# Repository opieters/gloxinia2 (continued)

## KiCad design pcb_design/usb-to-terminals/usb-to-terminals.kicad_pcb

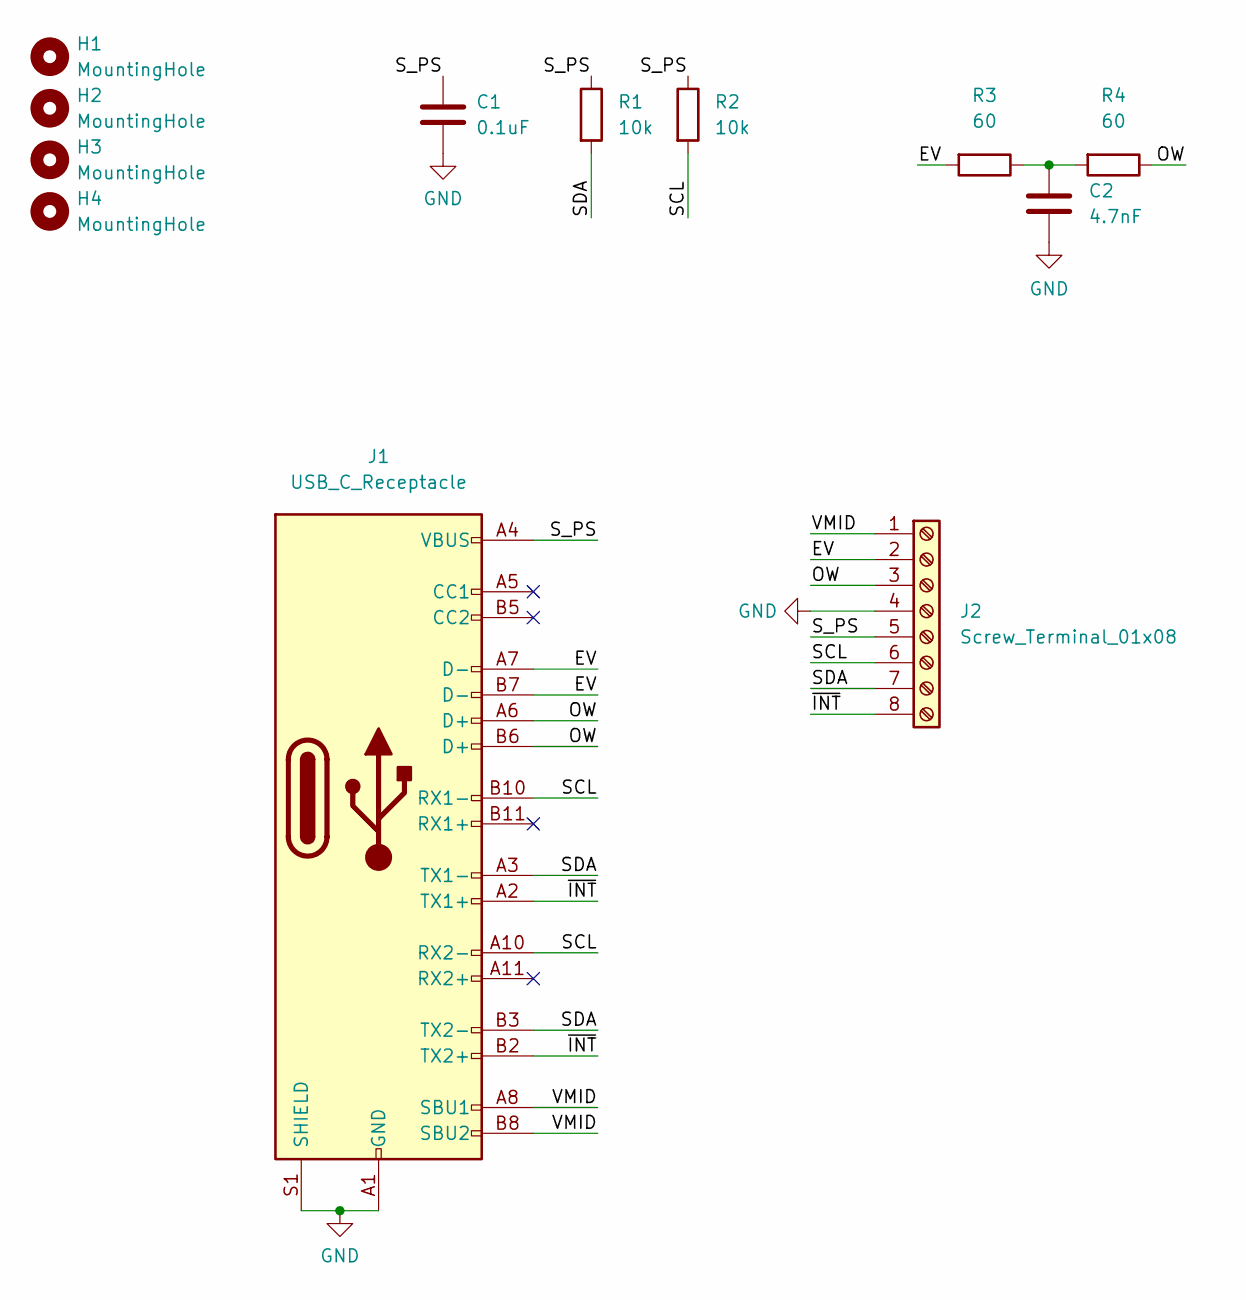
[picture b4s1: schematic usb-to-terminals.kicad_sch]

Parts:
C1: 0.1uF; C_0603_1608Metric; Voltage rating 16V; MPN C0603C104K4RAC7867
C2: 4.7nF; C_0603_1608Metric; Voltage rating 16V
H1, H2, H3, H4: MountingHole; MountingHole_3.2mm_M3
J1: USB_C_Receptacle; USB_C_Receptacle_Amphenol_12401861XX12A; MPN 124018612112A
J2: Screw_Terminal_01x08; TerminalBlock_Phoenix_PT-1,5-8-3.5-H_1x08_P3.50mm_Horizontal; MPN 1984646
R1, R2: 10k; R_0603_1608Metric
R3, R4: 60; R_0603_1608Metric

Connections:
/EV: J1.A7 (D-), J1.B7 (D-), J2.2, R3.2
/OW: J1.A6 (D+), J1.B6 (D+), J2.3, R4.1
/SCL: J1.A10 (RX2-), J1.B10 (RX1-), J2.6, R2.2
/SDA: J1.A3 (TX1-), J1.B3 (TX2-), J2.7, R1.2
/S_PS: C1.1, J1.A4 (VBUS), J1.A9 (VBUS), J1.B4 (VBUS), J1.B9 (VBUS), J2.5, R1.1, R2.1
/VMID: J1.A8 (SBU1), J1.B8 (SBU2), J2.1
/~INT: J1.A2 (TX1+), J1.B2 (TX2+), J2.8
GND: C1.2, C2.2, J1.A1 (GND), J1.A12 (GND), J1.B1 (GND), J1.B12 (GND), J1.S1 (SHIELD), J2.4
unnamed: C2.1, R3.1, R4.2

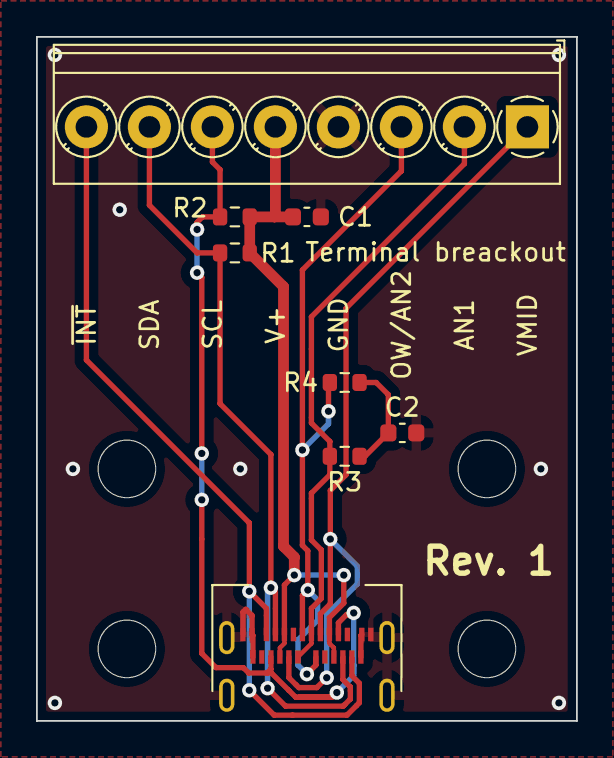
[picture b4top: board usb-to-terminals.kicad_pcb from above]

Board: 2 copper layers, 30.0 x 38.0 mm, 12 parts (0 on the bottom side), 9 nets.

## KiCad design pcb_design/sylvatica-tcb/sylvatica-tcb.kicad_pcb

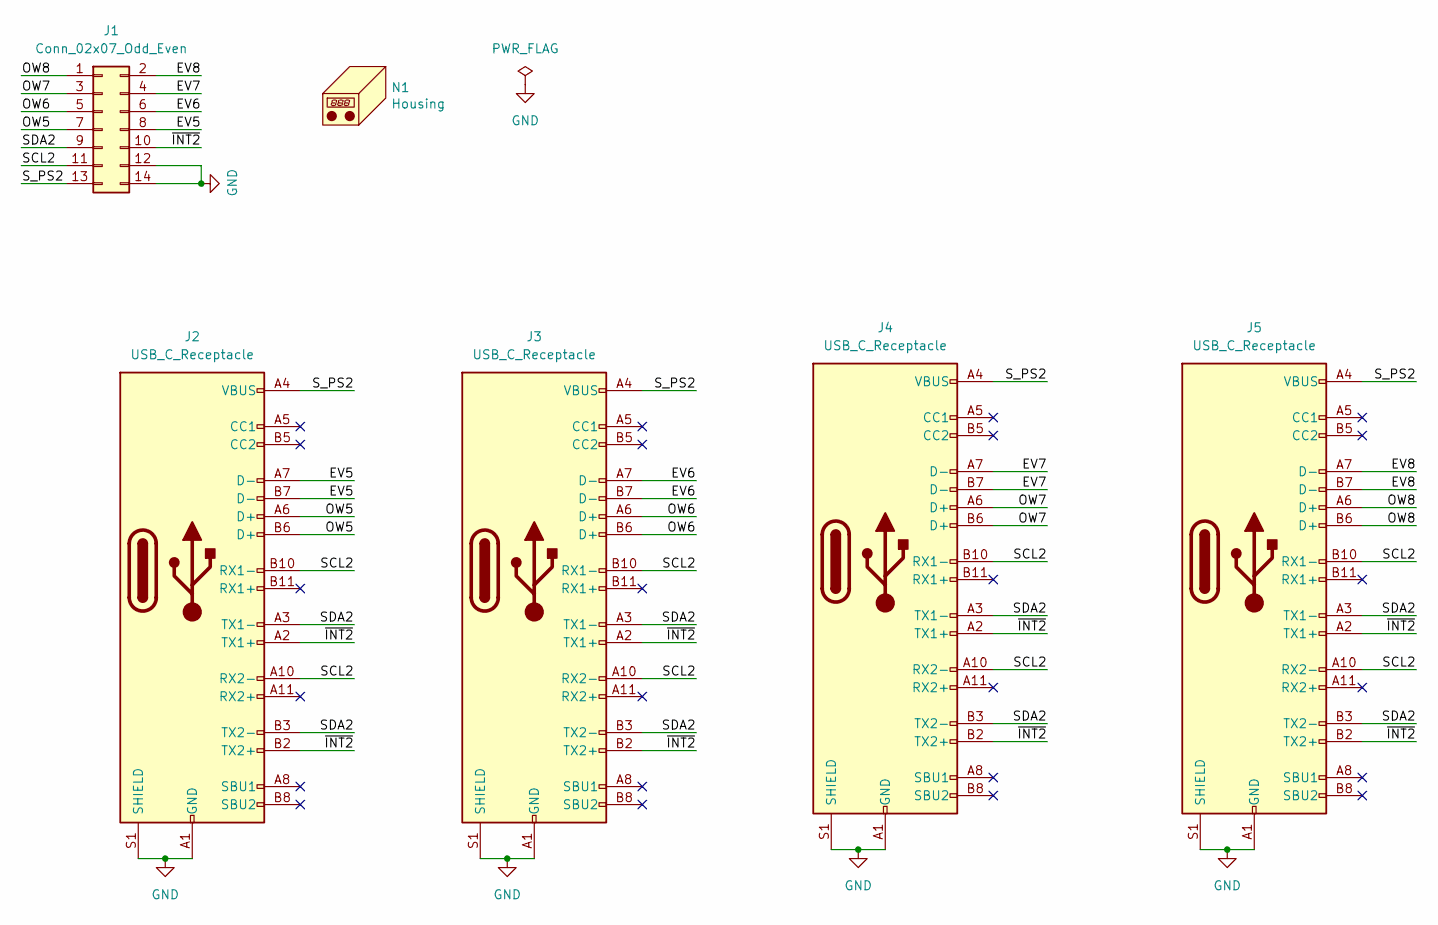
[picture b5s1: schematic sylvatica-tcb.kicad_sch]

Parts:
J1: Conn_02x07_Odd_Even; SAMTEC_TMMH-107-01-T-DV; MPN TMMH-107-01-T-DV
J2, J3, J4, J5: USB_C_Receptacle; USB_C_Receptacle_Amphenol_12401861XX12A; MPN 124018612112A
N1: Housing; Enclosure-Gloxinia4

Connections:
/EV5: J1.8, J2.A7 (D-), J2.B7 (D-)
/EV6: J1.6, J3.A7 (D-), J3.B7 (D-)
/EV7: J1.4, J4.A7 (D-), J4.B7 (D-)
/EV8: J1.2, J5.A7 (D-), J5.B7 (D-)
/OW5: J1.7, J2.A6 (D+), J2.B6 (D+)
/OW6: J1.5, J3.A6 (D+), J3.B6 (D+)
/OW7: J1.3, J4.A6 (D+), J4.B6 (D+)
/OW8: J1.1, J5.A6 (D+), J5.B6 (D+)
/SCL2: J1.11, J2.A10 (RX2-), J2.B10 (RX1-), J3.A10 (RX2-), J3.B10 (RX1-), J4.A10 (RX2-), J4.B10 (RX1-), J5.A10 (RX2-), J5.B10 (RX1-)
/SDA2: J1.9, J2.A3 (TX1-), J2.B3 (TX2-), J3.A3 (TX1-), J3.B3 (TX2-), J4.A3 (TX1-), J4.B3 (TX2-), J5.A3 (TX1-), J5.B3 (TX2-)
/S_PS2: J1.13, J2.A4 (VBUS), J2.A9 (VBUS), J2.B4 (VBUS), J2.B9 (VBUS), J3.A4 (VBUS), J3.A9 (VBUS), J3.B4 (VBUS), J3.B9 (VBUS), J4.A4 (VBUS), J4.A9 (VBUS), J4.B4 (VBUS), J4.B9 (VBUS), J5.A4 (VBUS), J5.A9 (VBUS), J5.B4 (VBUS), J5.B9 (VBUS)
/~INT2: J1.10, J2.A2 (TX1+), J2.B2 (TX2+), J3.A2 (TX1+), J3.B2 (TX2+), J4.A2 (TX1+), J4.B2 (TX2+), J5.A2 (TX1+), J5.B2 (TX2+)
GND: J1.12, J1.14, J2.A1 (GND), J2.A12 (GND), J2.B1 (GND), J2.B12 (GND), J2.S1 (SHIELD), J3.A1 (GND), J3.A12 (GND), J3.B1 (GND), J3.B12 (GND), J3.S1 (SHIELD), J4.A1 (GND), J4.A12 (GND), J4.B1 (GND), J4.B12 (GND), J4.S1 (SHIELD), J5.A1 (GND), J5.A12 (GND), J5.B1 (GND), J5.B12 (GND), J5.S1 (SHIELD)

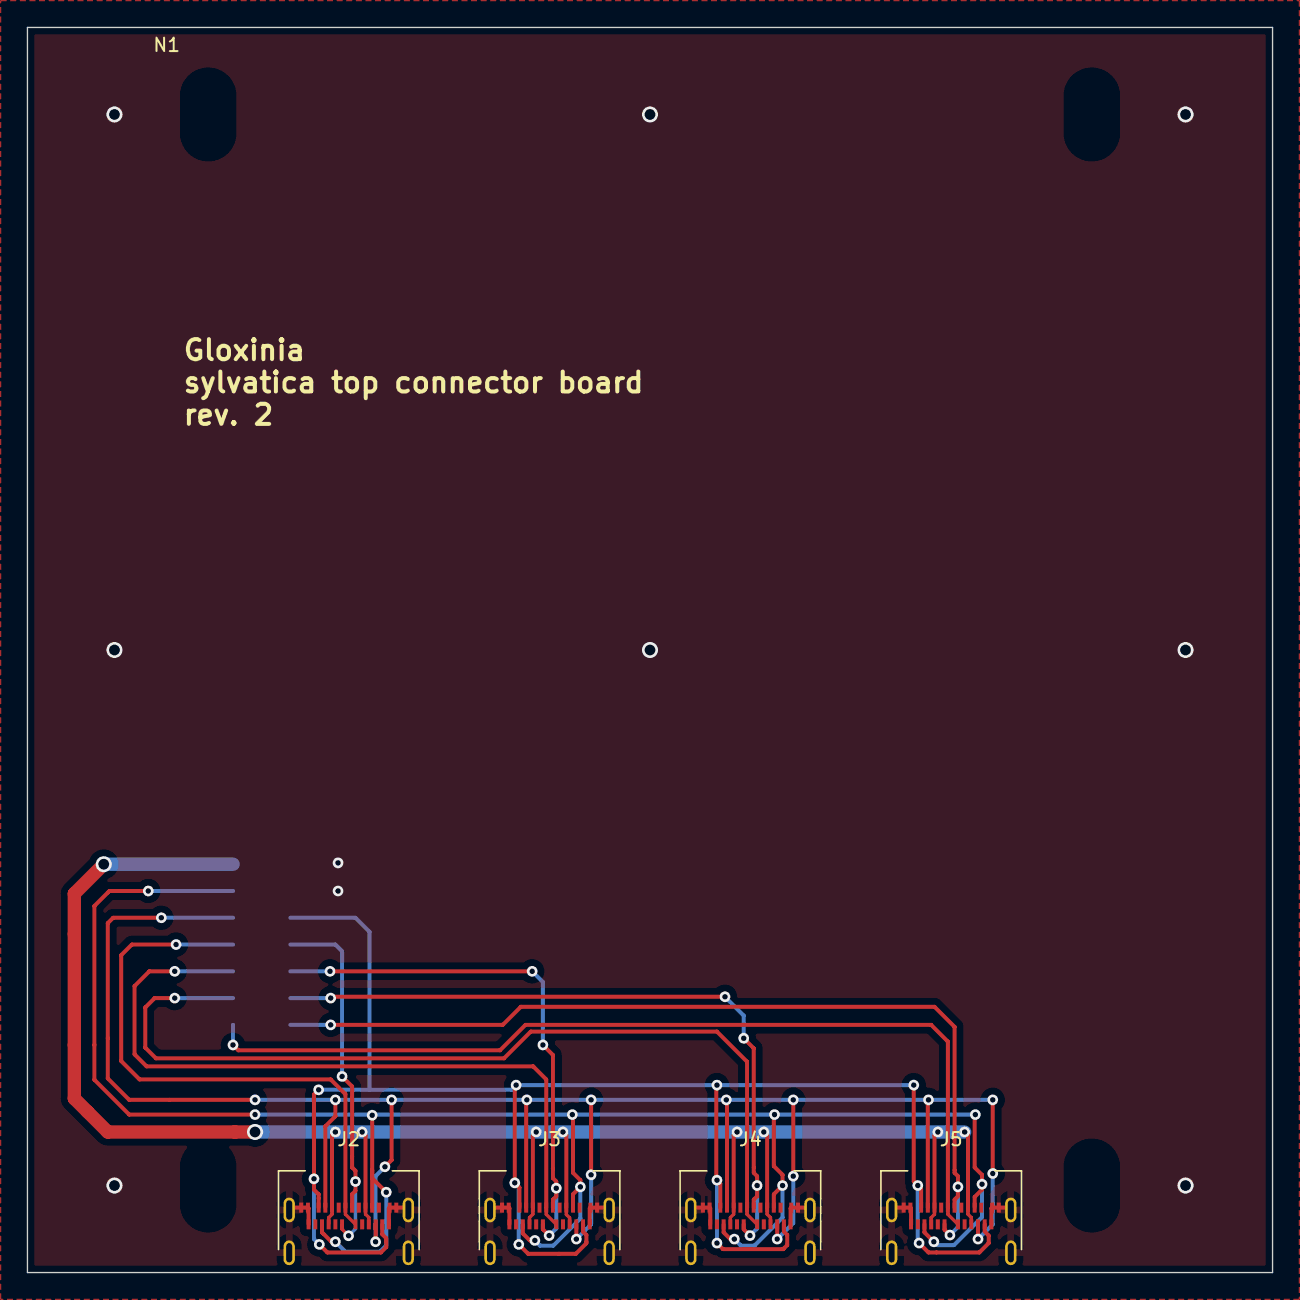
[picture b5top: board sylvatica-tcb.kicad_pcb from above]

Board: 2 copper layers, 93.0 x 93.0 mm, 6 parts (1 on the bottom side), 13 nets.

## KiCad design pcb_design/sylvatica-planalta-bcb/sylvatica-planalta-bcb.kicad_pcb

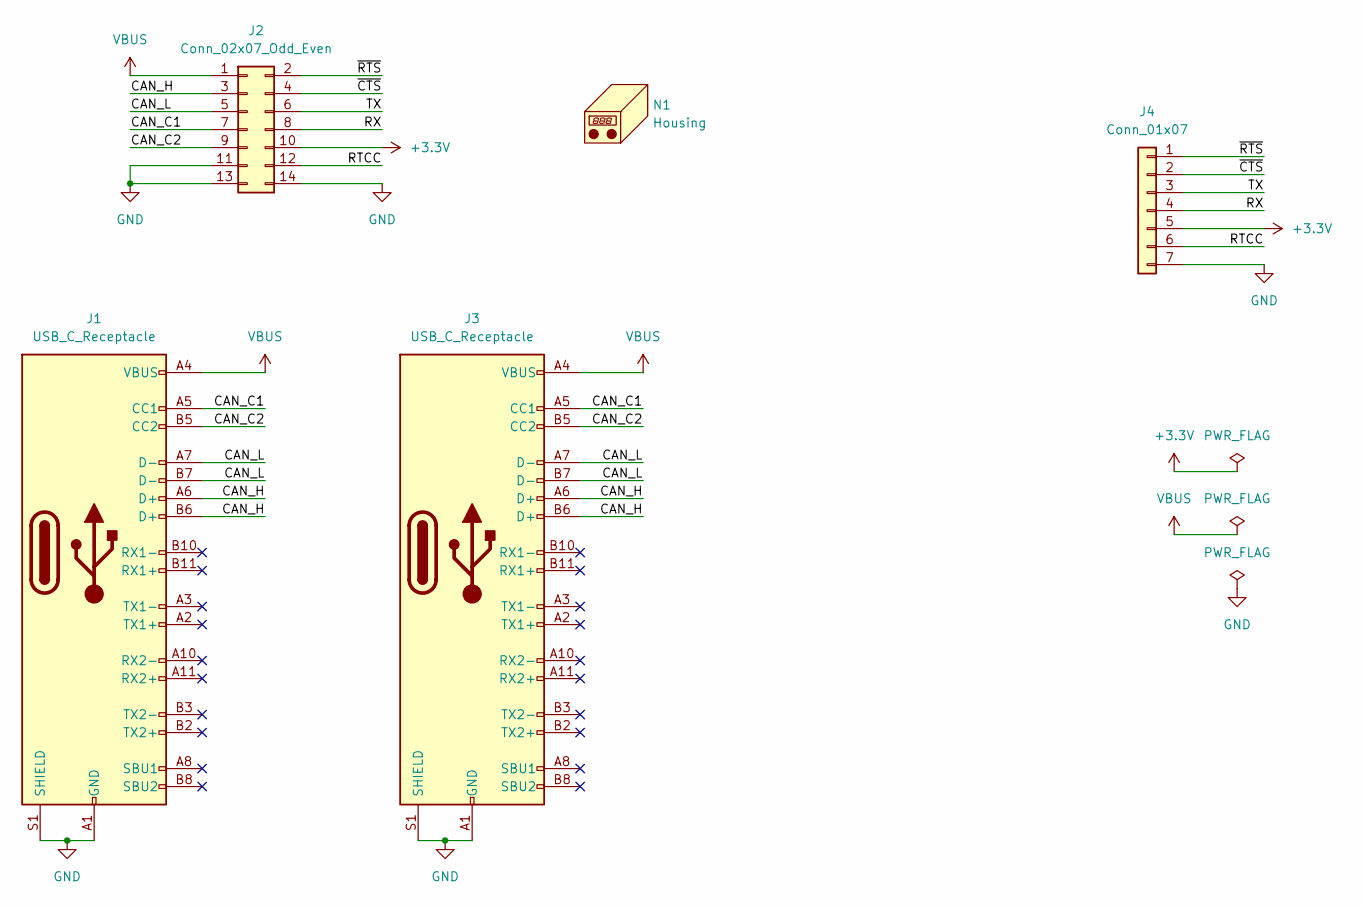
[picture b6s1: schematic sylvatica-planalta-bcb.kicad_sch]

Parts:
J1, J3: USB_C_Receptacle; USB_C_Receptacle_Amphenol_12401861XX12A; MPN 124018612112A
J2: Conn_02x07_Odd_Even; SAMTEC_MMS-107-02-F-DV; MPN MMS-107-02-F-DV
J4: Conn_01x07; PinHeader_1x07_P2.54mm_Vertical
N1: Housing; Enclosure-Gloxinia4

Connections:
+3.3V: J2.10, J4.5
/CAN_C1: J1.A5 (CC1), J2.7, J3.A5 (CC1)
/CAN_C2: J1.B5 (CC2), J2.9, J3.B5 (CC2)
/CAN_H: J1.A6 (D+), J1.B6 (D+), J2.3, J3.A6 (D+), J3.B6 (D+)
/CAN_L: J1.A7 (D-), J1.B7 (D-), J2.5, J3.A7 (D-), J3.B7 (D-)
/RTCC: J2.12, J4.6
/RX: J2.8, J4.4
/TX: J2.6, J4.3
/~CTS: J2.4, J4.2
/~RTS: J2.2, J4.1
GND: J1.A1 (GND), J1.A12 (GND), J1.B1 (GND), J1.B12 (GND), J1.S1 (SHIELD), J2.11, J2.13, J2.14, J3.A1 (GND), J3.A12 (GND), J3.B1 (GND), J3.B12 (GND), J3.S1 (SHIELD), J4.7
VBUS: J1.A4 (VBUS), J1.A9 (VBUS), J1.B4 (VBUS), J1.B9 (VBUS), J2.1, J3.A4 (VBUS), J3.A9 (VBUS), J3.B4 (VBUS), J3.B9 (VBUS)

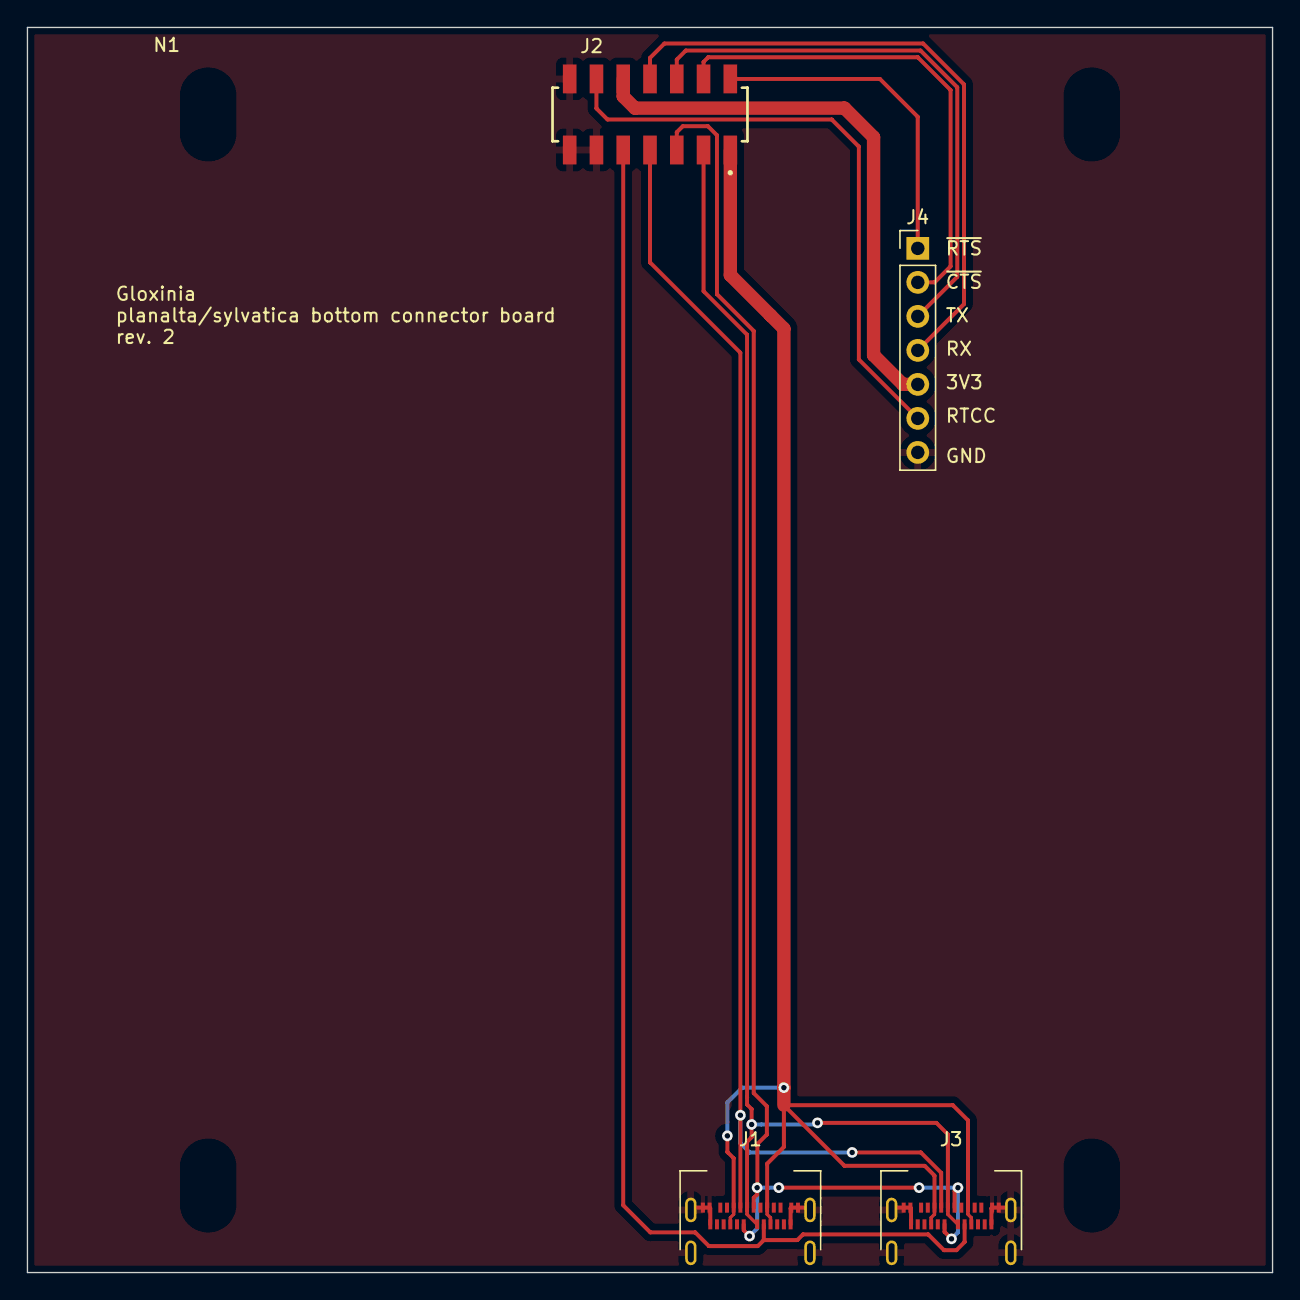
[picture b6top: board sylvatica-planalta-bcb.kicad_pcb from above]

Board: 2 copper layers, 93.0 x 93.0 mm, 5 parts (0 on the bottom side), 12 nets.

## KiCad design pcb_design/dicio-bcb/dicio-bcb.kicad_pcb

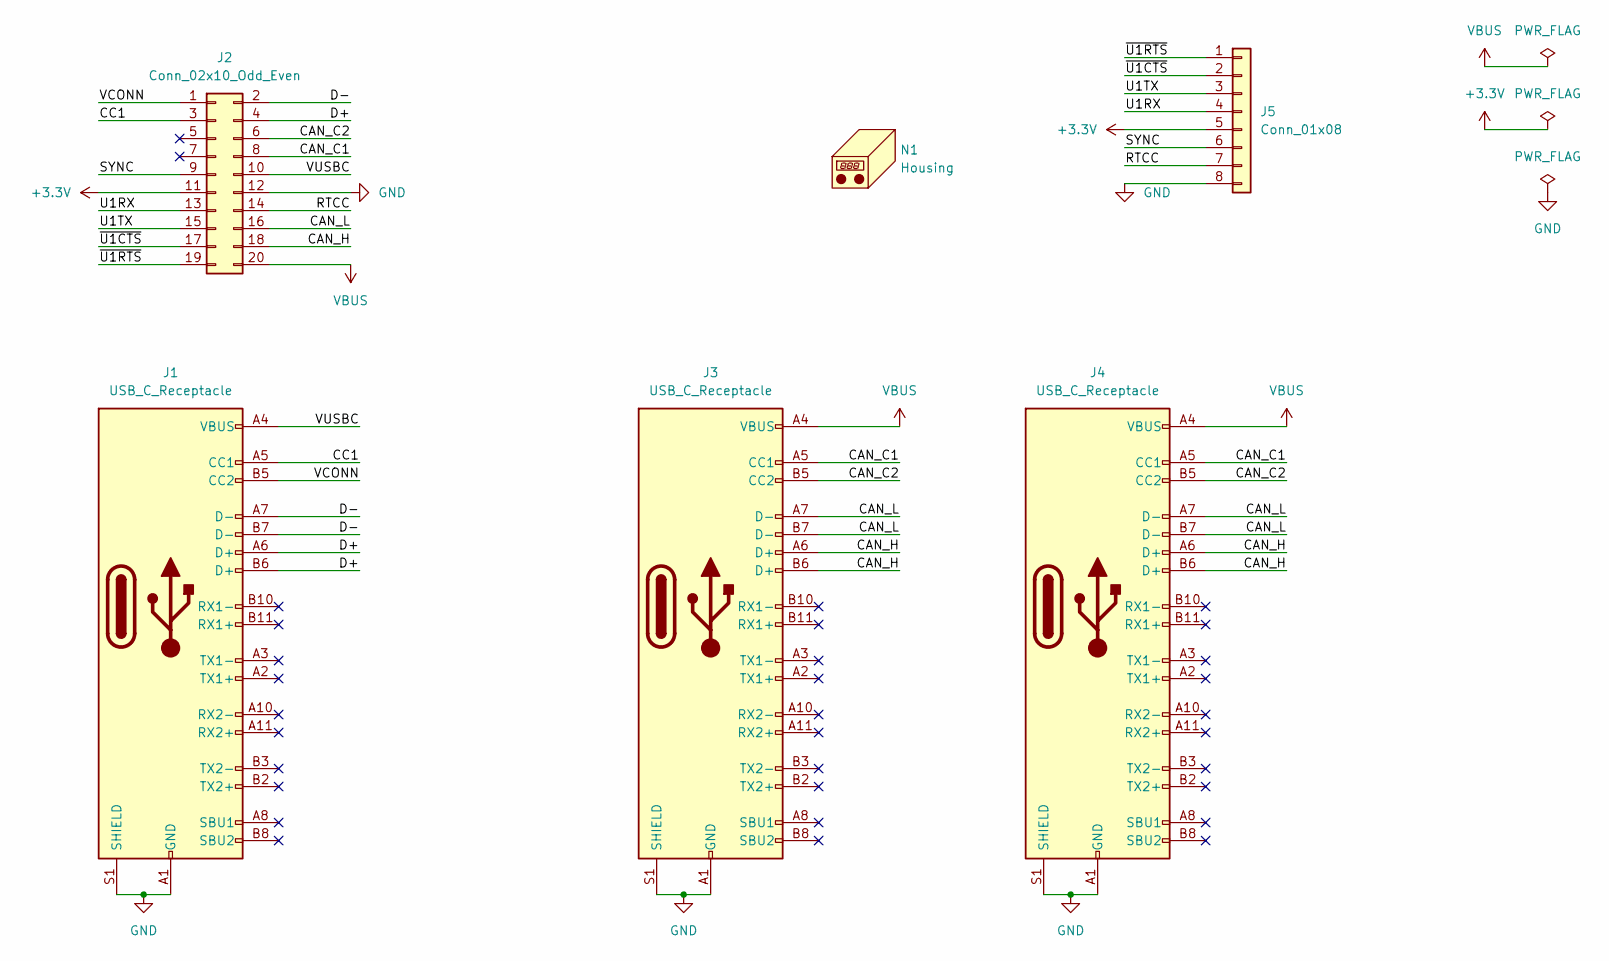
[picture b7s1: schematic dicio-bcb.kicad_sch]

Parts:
J1, J3, J4: USB_C_Receptacle; USB_C_Receptacle_Amphenol_12401861XX12A; MPN 124018612112A
J2: Conn_02x10_Odd_Even; SAMTEC-MMS-110-02-X-DV; MPN MMS-110-02-F-DV
J5: Conn_01x08; PinHeader_1x08_P2.54mm_Vertical
N1: Housing; Enclosure-Gloxinia4

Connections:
+3.3V: J2.11, J5.5
/CAN_C1: J2.8, J3.A5 (CC1), J4.A5 (CC1)
/CAN_C2: J2.6, J3.B5 (CC2), J4.B5 (CC2)
/CAN_H: J2.18, J3.A6 (D+), J3.B6 (D+), J4.A6 (D+), J4.B6 (D+)
/CAN_L: J2.16, J3.A7 (D-), J3.B7 (D-), J4.A7 (D-), J4.B7 (D-)
/CC1: J1.A5 (CC1), J2.3
/D+: J1.A6 (D+), J1.B6 (D+), J2.4
/D-: J1.A7 (D-), J1.B7 (D-), J2.2
/RTCC: J2.14, J5.7
/SYNC: J2.9, J5.6
/U1RX: J2.13, J5.4
/U1TX: J2.15, J5.3
/VCONN: J1.B5 (CC2), J2.1
/VUSBC: J1.A4 (VBUS), J1.A9 (VBUS), J1.B4 (VBUS), J1.B9 (VBUS), J2.10
/~U1CTS: J2.17, J5.2
/~U1RTS: J2.19, J5.1
GND: J1.A1 (GND), J1.A12 (GND), J1.B1 (GND), J1.B12 (GND), J1.S1 (SHIELD), J2.12, J3.A1 (GND), J3.A12 (GND), J3.B1 (GND), J3.B12 (GND), J3.S1 (SHIELD), J4.A1 (GND), J4.A12 (GND), J4.B1 (GND), J4.B12 (GND), J4.S1 (SHIELD), J5.8
VBUS: J2.20, J3.A4 (VBUS), J3.A9 (VBUS), J3.B4 (VBUS), J3.B9 (VBUS), J4.A4 (VBUS), J4.A9 (VBUS), J4.B4 (VBUS), J4.B9 (VBUS)

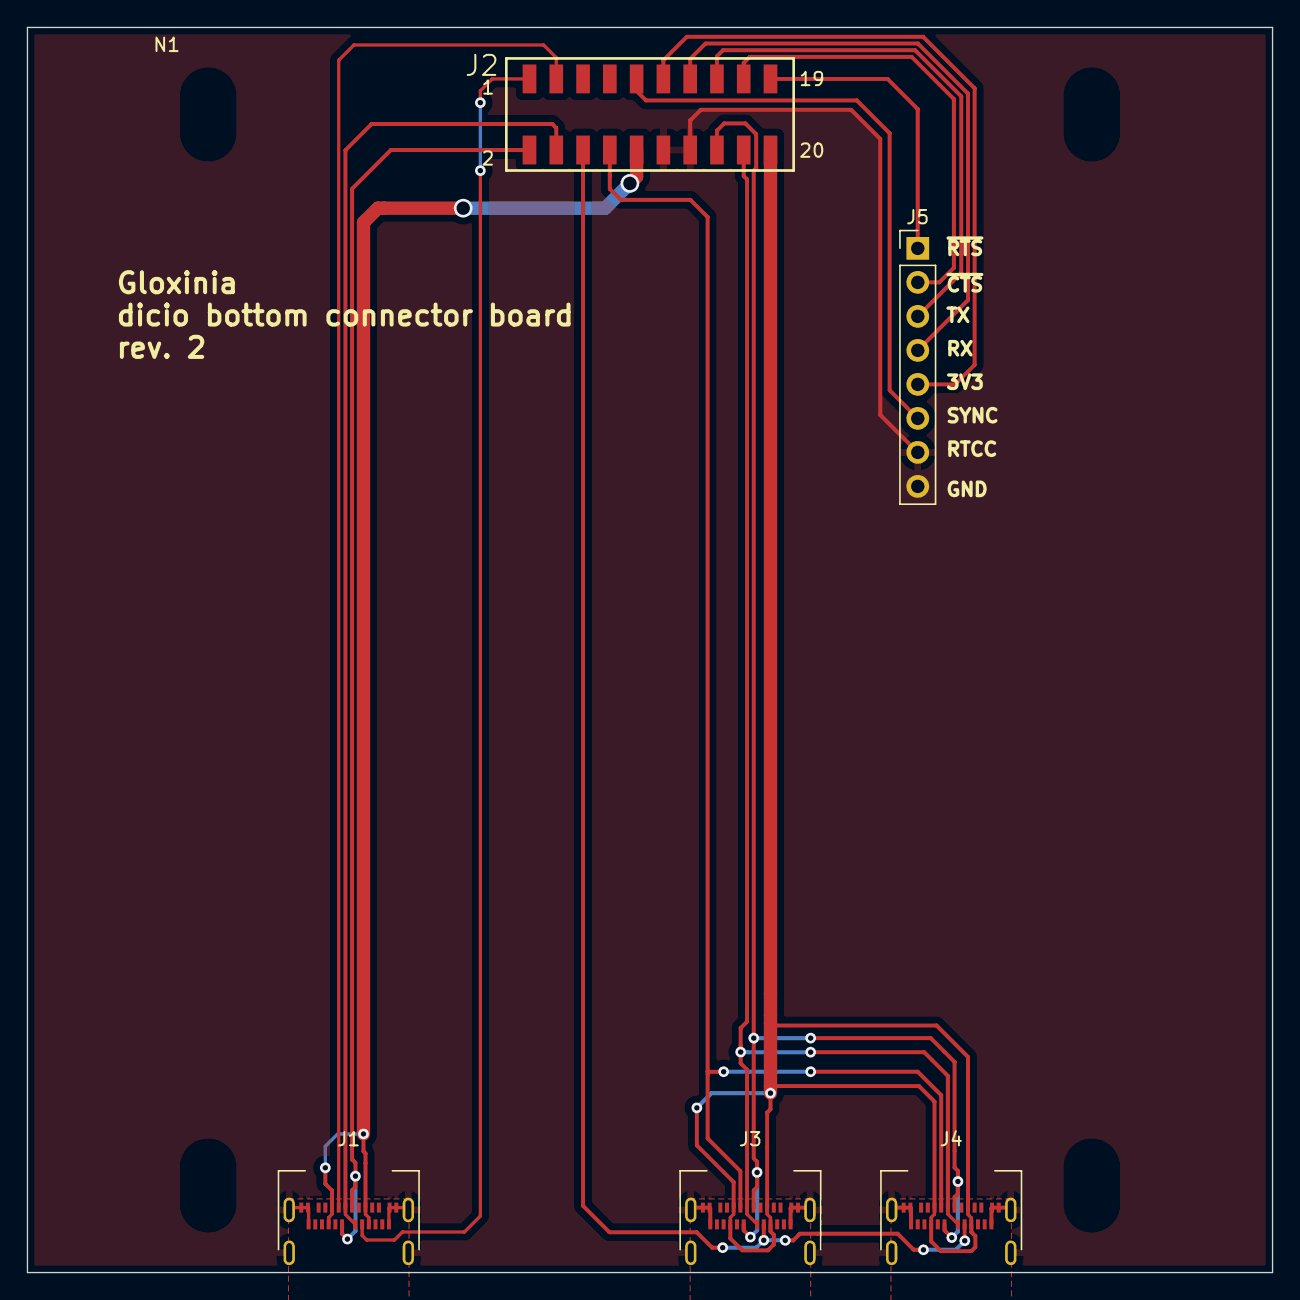
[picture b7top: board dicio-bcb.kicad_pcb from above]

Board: 2 copper layers, 93.0 x 93.0 mm, 6 parts (0 on the bottom side), 18 nets.
